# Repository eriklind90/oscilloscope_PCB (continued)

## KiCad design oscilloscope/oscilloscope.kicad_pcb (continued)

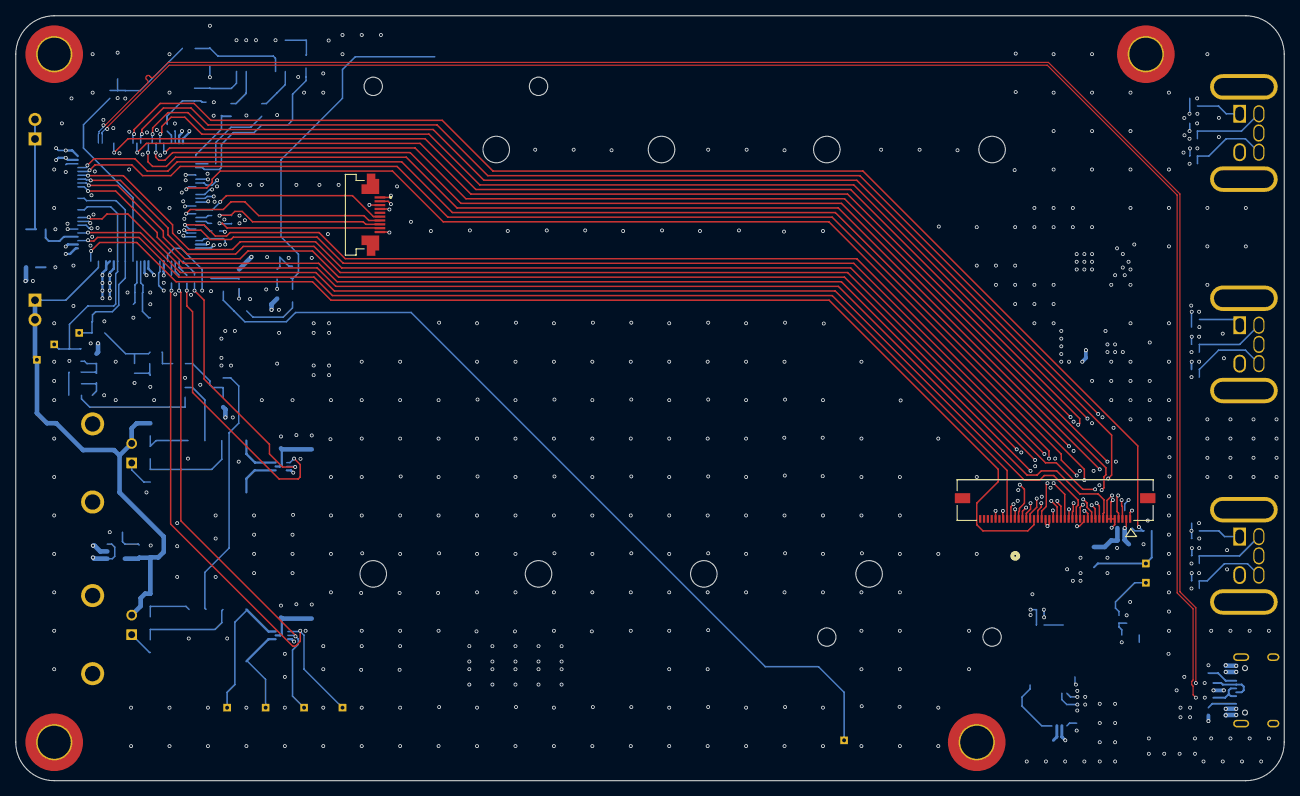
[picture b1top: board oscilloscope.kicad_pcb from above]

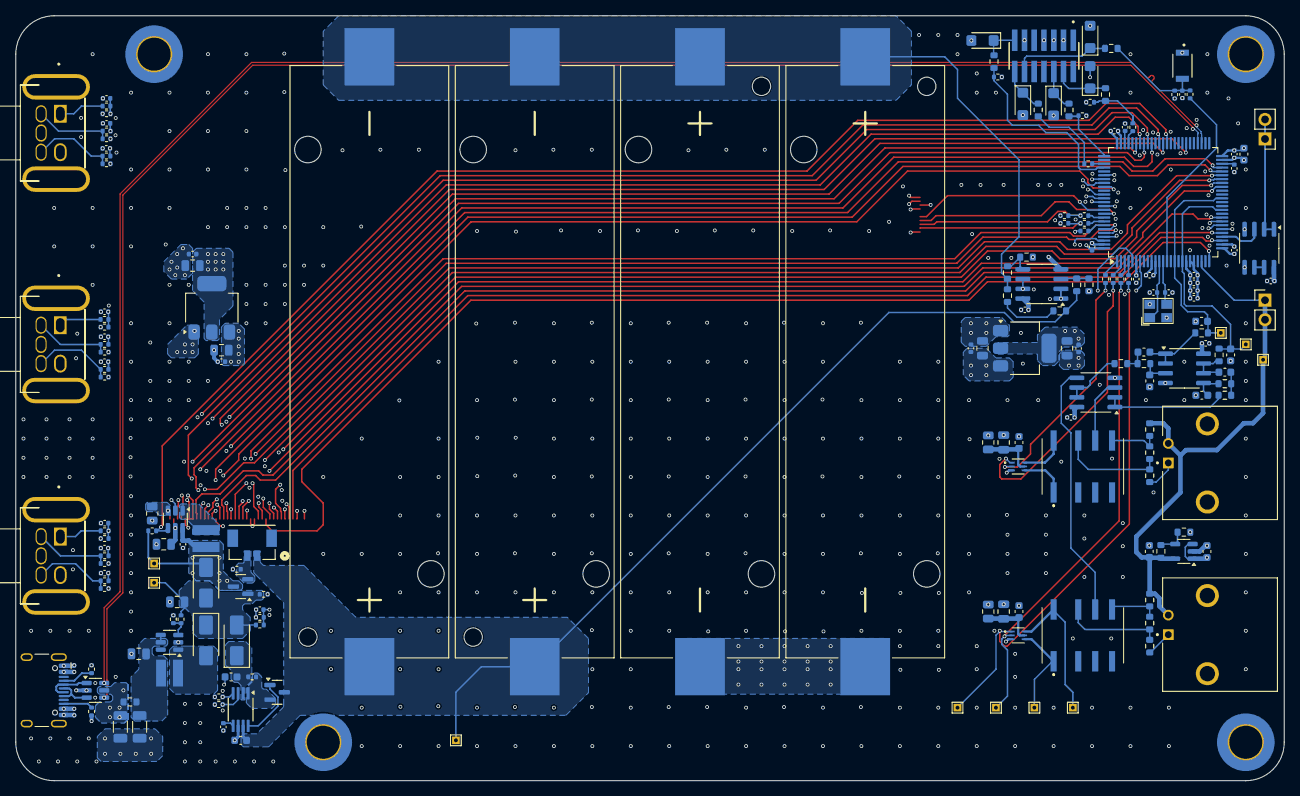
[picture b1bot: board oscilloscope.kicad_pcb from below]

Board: 6 copper layers, 165.0 x 99.5 mm, 194 parts (192 on the bottom side), 134 nets.

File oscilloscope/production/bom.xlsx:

Designator | Footprint | Quantity | Value | LCSC Part # | Digikey
BT1, BT2, BT3, BT4 | BH_18650_1042 | 4 | Battery_Cell | C5249310
C1, C16, C45 | 402 | 3 | 1u | C52923
C10 | 603 | 1 | 4u7 | C19666
C11, C15, C17, C23, C33, C38, C39, C40, C41, C42, C43, C44, C49, C50, C51, C54,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 | 402 | 19 | 100n | C307331
C12, C18 | 402 | 2 | 15p | C1548
C13, C14, C22, C35, C47, C48, C52, C53 | 805 | 8 | 22u | C45783
C19, C36 | 603 | 2 | 110p | C519568
C2, C3 | 402 | 2 | 2u2 | C12530
C20, C37 | 603 | 2 | 220p | C519500
C21, C34 | 603 | 2 | 100n | C14663
C24, C25, C26, C27, C28, C29, C30, C31, C32 | 402 | 9 | 10n | C15195
C4 | 603 | 1 | 470n | C1623
C46 | 805 | 1 | 220n | C5378
C5, C6 | 1206 | 2 | 47u | C96123
C58, C59 | 603 | 2 | 150p | C1594
C7, C8 | 603 | 2 | 10u | C96446
C9 | 603 | 1 | 2u2 | C23630
D1, D2, D3, D4, D8 | D_SMF | 5 | SMF5V0A | C1972946
D5, D6, D7 | D_SMA | 3 | SS34 | C8678
FB10 | 603 | 1 | BLM18PG121SN1D | C14709
FB2, FB3, FB4, FB5, FB6 | 603 | 5 | GZ1608D601TF | C1002
J1 | CON_5051104091_MOL | 1 | 5051104091 | x | 5051104091
J3 | SAMTEC_FTSH-107-01-X-DV-K | 1 | Conn_ST_STDC14 | x | FTSH-107-01-L-DV-K
J4, J7 | LINX_CONBNC002 | 2 | Conn_Coaxial | x | CONBNC002
J5, J8 | PinHeader_1x02_P2.54mm_Vertical | 2 | Conn_01x02_Pin | x | x
J6 | USB_C_Receptacle_HCTL_HC-TYPE-C-16P-01A | 1 | TYPE-C 16PIN 2MD(073) | C2894897
J9 | AMPHENOL_SFV10R-2STE1HLF | 1 | SFV10R-2STE1HLF | x | SFV10R-2STE1HLF
L2, L3 | SRN3012BTA | 2 | 22u | C19947585
Q1, Q3 | SOT-23 | 2 | AO3401A | C15127
R1, R2 | 402 | 2 | 5k1 | C25905
R10 | 402 | 1 | 470k | C25790
R11, R14 | 603 | 2 | 270k | x | x
R12, R16 | 603 | 2 | 50k | x | x
R13, R15 | 603 | 2 | 680k | x | RT0603BRD07680KL
R17 | 603 | 1 | 113k | x | ERA-3AEB1133V
R18 | 603 | 1 | 169k | x | ERA-3AEB1693V
R19, R33, R40, R41, R42, R43, R46, R47 | 402 | 8 | 47R | C25118
R20, R21, R22, R23 | 603 | 4 | 1k69 | x | ERA-3AEB1691V
R24, R25, R26, R27, R28, R29, R30, R31, R32, R39, R4, R48, R49, R54, R55, R56, 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 | 402 | 22 | 10k | C25744
R3, R36, R5, R50 | 402 | 4 | 100k | C25741
R34, R35 | 805 | 2 | 47R | C17714
R37 | 402 | 1 | 1k | C11702
R38 | 402 | 1 | 47k | C25792
R44, R45 | 402 | 2 | 4k7 | C25900
R51 | 402 | 1 | 33K | C25779
R52, R63, R65 | 603 | 3 | 560K | C23203
R53 | 603 | 1 | 200K | C25811
R6 | 805 | 1 | 6R2 | x | RK73H2ATTD6R20F
R64, R66 | 603 | 2 | 430k | C25969
R67 | 402 | 1 | 1M | C26083
R68, R69 | 603 | 2 | 47R | C23182
R7 | 402 | 1 | 51k | C25794
R8 | 402 | 1 | 3k3 | C25890
R9 | 402 | 1 | 100m | x
SW1, SW2, SW3 | XDCR_PEC12R-2220F-S0024 | 3 | RotaryEncoder_Switch | x | PEC12R-2220F-S0024-ND
SW4 | CONN_505567_02_MOL | 1 | SW_DIP_x01 | x | 5055670271 | 5055650201
SW5 | SW_B3U-1000P | 1 | SW_Push | x
TP10 | TestPoint_THTPad_1.0x1.0mm_Drill0.5mm | 1 | 9.7V | x
TP11 | TestPoint_THTPad_1.0x1.0mm_Drill0.5mm | 1 | VBAT | x
TP12 | TestPoint_THTPad_1.0x1.0mm_Drill0.5mm | 1 | CH1_B_DVR_1 | x
TP3 | TestPoint_THTPad_1.0x1.0mm_Drill0.5mm | 1 | IN2_FILT | x
TP4 | TestPoint_THTPad_1.0x1.0mm_Drill0.5mm | 1 | IN1_FILT | x
TP5 | TestPoint_THTPad_1.0x1.0mm_Drill0.5mm | 1 | CH1_B_DVR_2 | x
TP6 | TestPoint_THTPad_1.0x1.0mm_Drill0.5mm | 1 | GNDREF | x
TP7 | TestPoint_THTPad_1.0x1.0mm_Drill0.5mm | 1 | CH1_B_OUT1 | x
TP8 | TestPoint_THTPad_1.0x1.0mm_Drill0.5mm | 1 | CH1_B_OUT2 | x
TP9 | TestPoint_THTPad_1.0x1.0mm_Drill0.5mm | 1 | VDD | x
U1 | SOT-23-6 | 1 | USBLC6-2SC6 | C2827654
U10, U14 | SOT-223-3_TabPin2 | 2 | AMS1117-3.3 | C6186
U11, U15 | SOIC-8_3.9x4.9mm_P1.27mm | 2 | AD8646 | x | AD8646ARMZ-REEL
U12, U6 | AGQ21TA03X | 2 | AGQ210A06 | x | AGQ210A06
U13, U8 | SOT6_DRV8212_TEX | 2 | DRV8212DRL | x | DRV8212DRLR
U16, U9 | SOIC-8_3.9x4.9mm_P1.27mm | 2 | MCP6002T-I/SN | C7377
U2 | SOT-23-5 | 1 | TPS76301 | x | TPS76301DBVR
U3 | SOT-23-6 | 1 | MT3608 | x | TPS76301DBVR
U4 | MSOP-8_3x3mm_P0.65mm | 1 | MCP73844 | x | MCP73844T-840I/MS
U5 | LQFP-100_14x14mm_P0.5mm | 1 | STM32H750VBTx | C404010
U7 | TSOT-23-6 | 1 | AP3019A | x | AP3019AKTR-G1
Y1 | X322525MOB4SI | 1 | X322525MOB4SI | C9006

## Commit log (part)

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2025-12-29 schematic done
2025-12-30 Adding battery holders. Adding charing on/off ctrl to uC. Adding mid voltage sense of battery package.
2026-03-10 Close to finished
2026-03-17 finished?
2026-03-18 done?
